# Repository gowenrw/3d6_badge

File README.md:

# 3d6 Badge

This is where all the files for the 3d6 Badge will be stored.  
This includes code and art and cad and fab files.  All the things.

## File Structure

This is the file structure of this repository

* [/](/README.md) - YOU ARE HERE
* [/art/](./art/) - Artwork and other graphics created by this project
  * /art/inspiration/ - Art and graphics pulled from other sources used as inspiration for this project
* [/code/](./code/) - All project related Code / Firmware
  * /code/altbier_pcb/ - Code folder for the production PCB(s)
  * /code/include/ - Common code includes (e.g. chipset drivers, etc.) used by the other code folders
* [/docs/](./docs/) - Documentation created by this project including web pages
* [/eda/](./eda/) - Electronic Design Automation files (i.e. KiCad)
  * /eda/altbier_pcb_3d6/ - KiCad project folder for the named project PCB(s)
* [/reference_parts/](./reference_parts/) - Documentation pulled from other sources related to components
* [./README.md](/README.md) - This File
* [./LICENSE](/LICENSE) - Currently set to MIT

Note: the reference_parts directory a link to a submodule repository.
To add it use the following cmd after downloading this template:
```
git submodule add https://github.com/gowenrw/reference_parts reference_parts
```
This will make a link to the current commit of that repo.
To update it to a newer commit after its been added use this cmd:
```
git submodule update --recursive
```

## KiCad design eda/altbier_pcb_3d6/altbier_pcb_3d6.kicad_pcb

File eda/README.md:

# Electronic Design Automation

This is where all the Electronic Design Automation files for the PCB(s) will be stored.
The EDA used is KiCad 5.x unless otherwise specified.

The KiCad projects have been configured to use local libraries for long term sustainability per the best practices listed [HERE](https://hackaday.com/2017/05/18/kicad-best-practises-library-management/) and elsewhere.

## File Structure

This is the file structure of this repository

* [/](/README.md) - Home
* [/eda](/eda/) - YOU ARE HERE
  * /eda/altbier_pcb_<project>/ - KiCad project folder for the named project PCB(s)
    * ./3d_models/ - This directory contains footprint 3d model files
    * ./gerber/ - This directory contains gerber formatted files for manufacturing
    * ./lib_fp/ - This directory contains footprint module directories
    * ./lib_sh/ - This directory contains schematic library files
    * ./snapshots/ - This directory contains prints of schematic / cad files and images of preview / final product

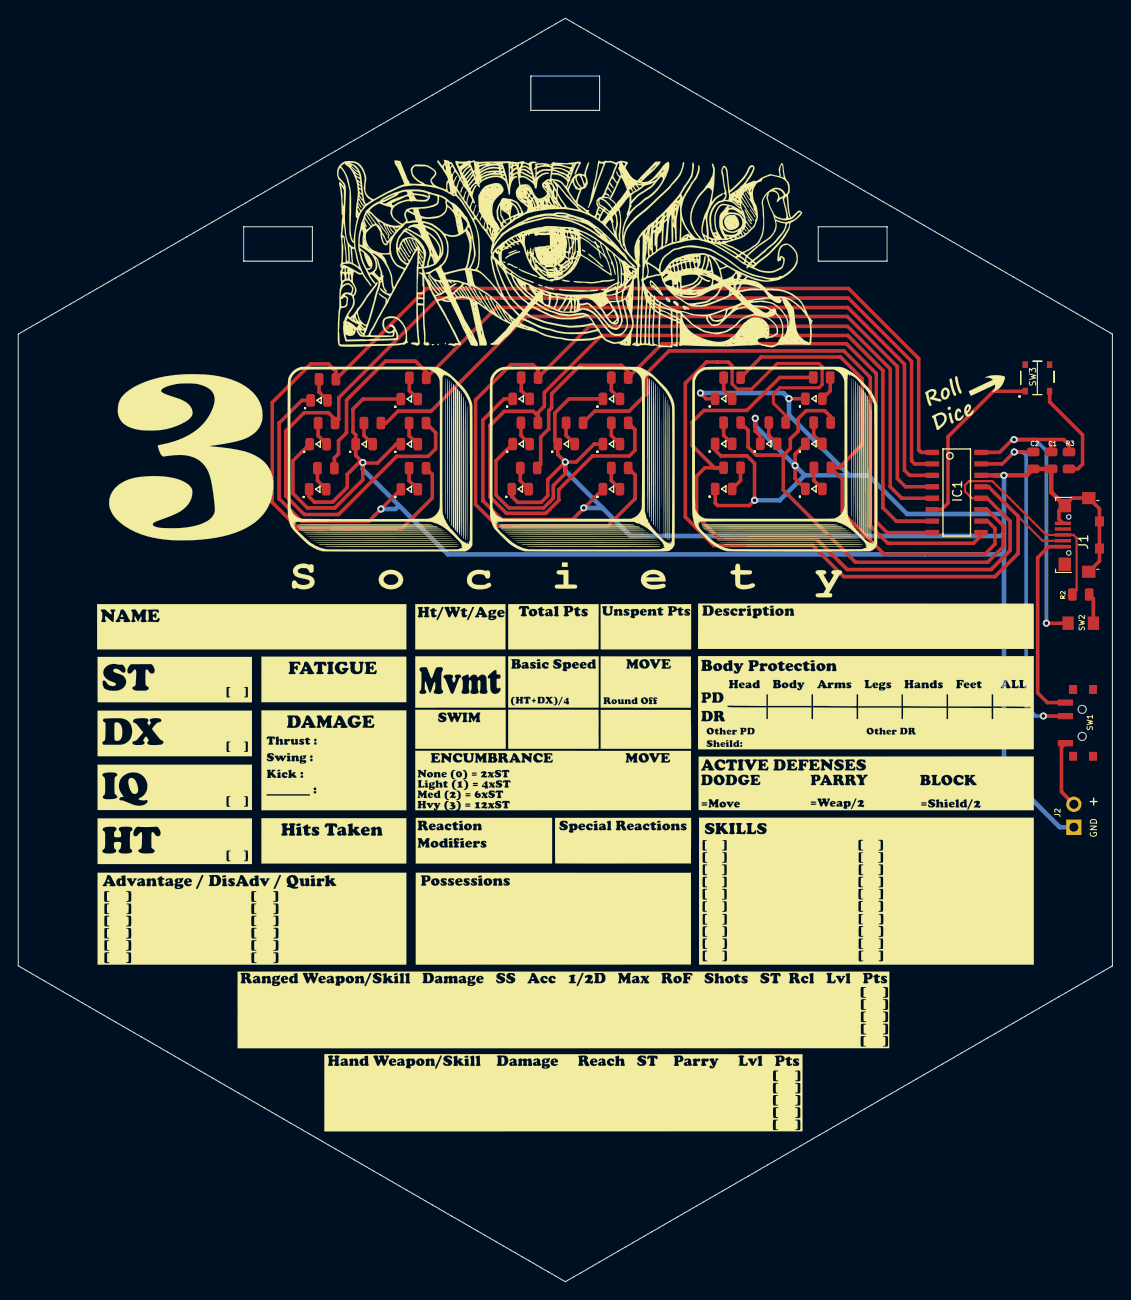
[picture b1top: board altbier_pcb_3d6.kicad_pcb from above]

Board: 2 copper layers, 121.2 x 140.0 mm, 54 parts (0 on the bottom side), 41 nets.

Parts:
3d6: LOGO; 3d6_front_silk_925
C1, C2: 0.1uF/100nF; C_0805_2012Metric_low-silk
D11, D12, D13, D14, D15, D16, D17, D21, D22, D23, D24, D25, D26, D27, D31, D32, D33, D34, D35, D36, D37: Blue; LED_0805_2012Metric_low-silk
Elliott1: LOGO; Elliott_front_silk_675
IC1: IC_CH552G; IC_SOIC-16_3.9x9.9mm_Pitch1.27mm
J1: USB_B_Micro; USB_Micro-B_Jing
J2: Conn_01x02; Conn_Pin_Header_Straight_1x02_Pitch2.54mm_low-silk
R2, R3: 10k Ohms; R_0805_2012Metric_low-silk
R11, R12, R13, R14, R15, R16, R17, R21, R22, R23, R24, R25, R26, R27, R31, R32, R33, R34, R35, R36, R37: 200 Ohms; R_0805_2012Metric_low-silk
SW1: SPDT_C136659; SW_SPDT_PCM12_C136659_low-silk
SW2: TS2306A; SW_TS2306A240GFMSM9_C388290_low-silk
SW3: SW_Push_SPST_4pin; SW_TS3735PA250GF

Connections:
BAT-PWR: J2.2, SW1.1
D+: IC1.12, J1.3, R2.1, R35.2, R36.2
D-: IC1.13, J1.2, R37.2
GND: C1.1, C2.1, D11.1, D12.1, D13.1, D14.1, D15.1, D16.1, D17.1, D21.1, D22.1, D23.1, D24.1, D25.1, D26.1, D27.1, D31.1, D32.1, D33.1, D34.1, D35.1, D36.1, D37.1, IC1.14, J1.5, J1.6, J2.1
unnamed: D11.2, R11.1
unnamed: D12.2, R12.1
unnamed: D13.2, R13.1
unnamed: D14.2, R14.1
unnamed: D15.2, R15.1
unnamed: D16.2, R16.1
unnamed: D17.2, R17.1
unnamed: D21.2, R21.1
unnamed: D22.2, R22.1
unnamed: D23.2, R23.1
unnamed: D24.2, R24.1
unnamed: D25.2, R25.1
unnamed: D26.2, R26.1
unnamed: D27.2, R27.1
unnamed: D31.2, R31.1
unnamed: D32.2, R32.1
unnamed: D33.2, R33.1
unnamed: D34.2, R34.1
unnamed: D35.2, R35.1
unnamed: D36.2, R36.1
unnamed: D37.2, R37.1
unnamed: R2.2, SW2.2
unnamed: R3.1, SW3.3
P1.1: IC1.9, R27.2
P1.4: IC1.2, R13.2, R14.2
P1.5: IC1.3, R15.2, R16.2
P1.6: IC1.4, R17.2
P1.7: IC1.5, R21.2, R22.2
P3.0: IC1.8, R25.2, R26.2
P3.1: IC1.7, R23.2, R24.2
P3.2: IC1.1, R11.2, R12.2
P3.3: IC1.10, R31.2, R32.2
P3.4: IC1.11, R33.2, R34.2
RST: IC1.6, SW3.1
USB-PWR: J1.1, SW1.3
V33: C1.2, IC1.16, R3.2, SW2.1
VCC: C2.2, IC1.15, SW1.2

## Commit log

2021-02-14 Initial Template Load
2021-02-14 Added reference_parts submodule
2021-02-15 schematic work
2021-02-18 test die blink code
2021-02-18 expanded 3d6 test
2021-02-19 Added code to set USB pins to GPIO
2021-02-22 Got psedo random working by writing seed to flash
2021-02-23 schematic rework with new button
2021-02-24 working count and roll die code and cleanup
2021-02-24 updated_reference_parts
2021-02-27 Principal artwork finished and added to PCB
2021-02-27 preparing docs dir for website
2021-02-27 Set theme jekyll-theme-midnight
2021-02-27 Create CNAME
2021-02-27 Update CNAME
2021-03-01 Artwork and PCB silkscreen updates
2021-03-01 final pcb updates and gerber plots for prototype run
2021-03-09 art for lanyard
2021-03-09 Updated design to allow for dual connect lanyard.
2021-03-18 Roll code updates to random seed interaction
2021-06-02 Documentation Updates
2021-07-09 Docs update
2021-08-17 doc updates, added some pics
2022-09-14 flash values
